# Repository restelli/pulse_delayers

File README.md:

# Pulse delay.
This is a PCB to test four delay chips.
I put it together in a couple of hours for a dirty test, but if further refined it could become a handy lab tool.
(Note that the SMA and power connectors are intentionally placed on the wrong side of the board)

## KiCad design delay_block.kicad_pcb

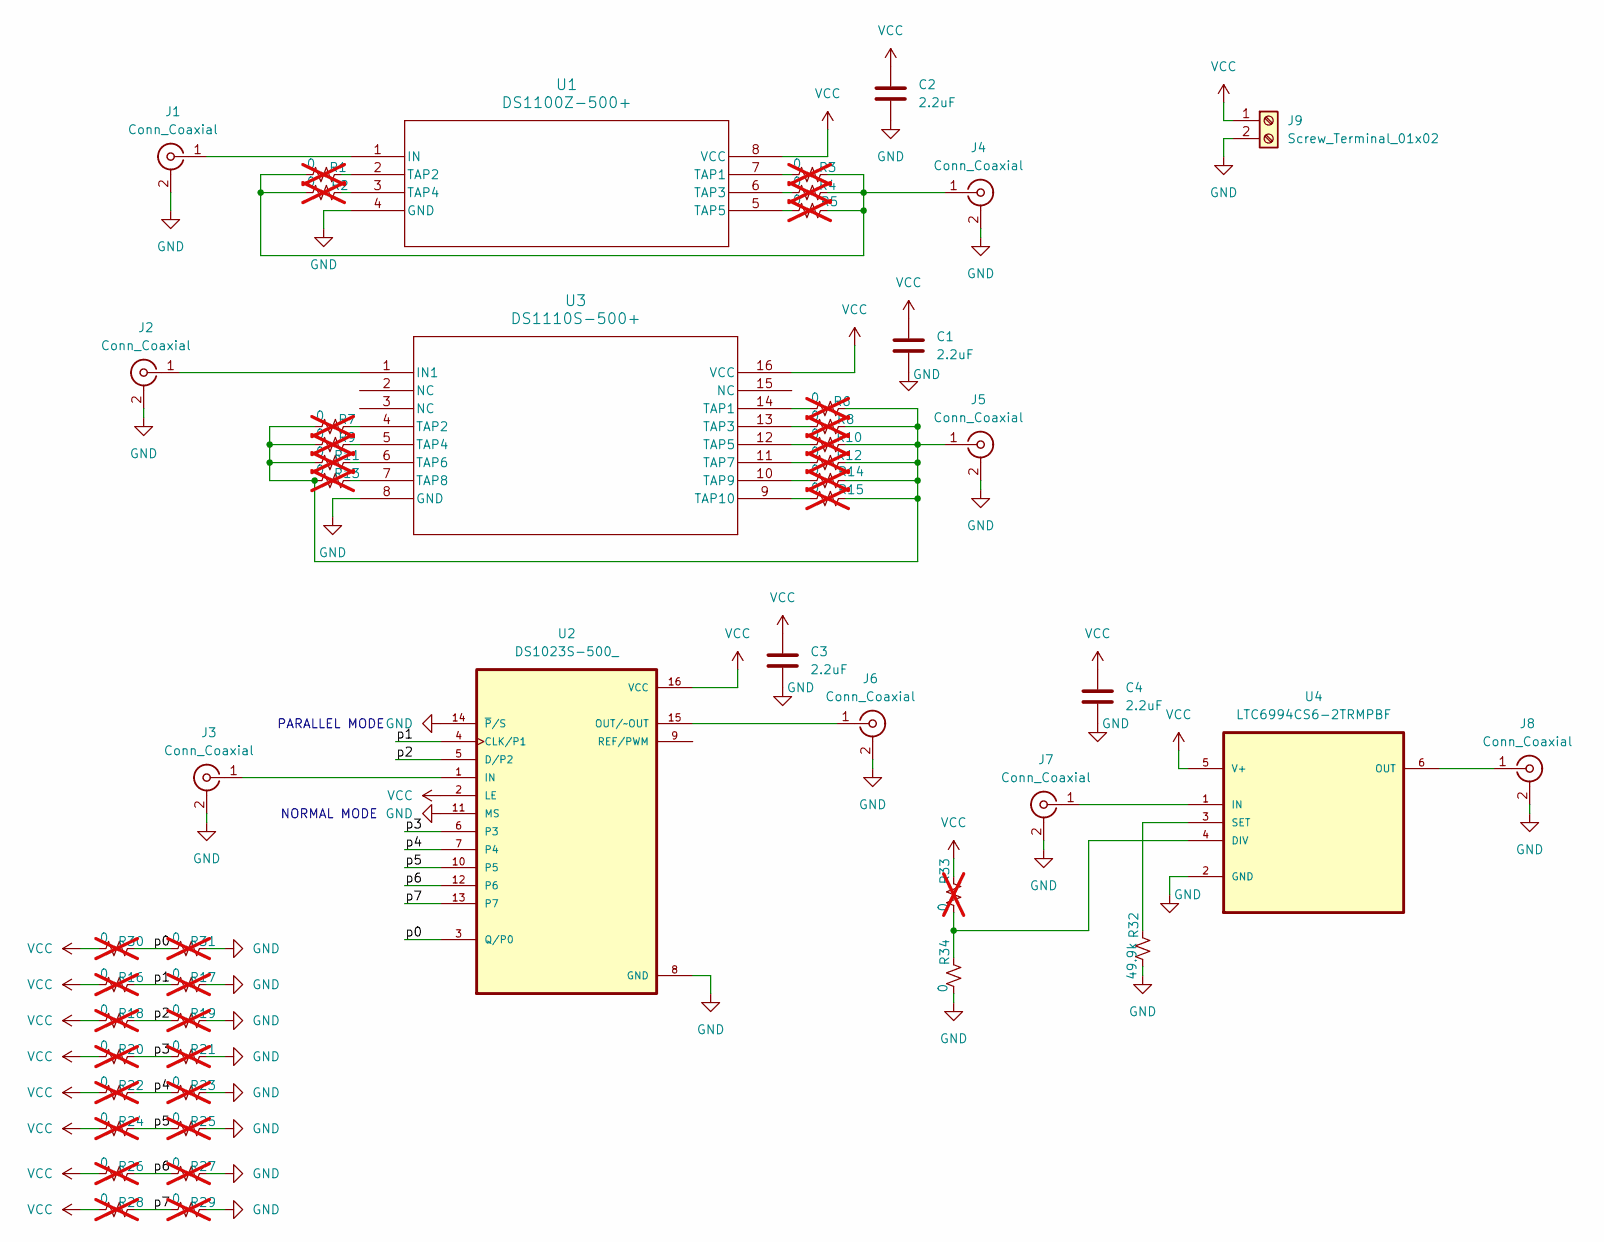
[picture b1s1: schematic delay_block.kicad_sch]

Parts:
C1, C2, C3, C4: 2.2uF; C_0805_2012Metric
J1, J2, J3, J4, J5, J6, J7, J8: Conn_Coaxial; SMA_Amphenol_901-144_Vertical
J9: Screw_Terminal_01x02; TerminalBlock_4Ucon_1x02_P3.50mm_Horizontal
R1, R2, R3, R4, R5, R6, R7, R8, R9, R10, R11, R12, R13, R14, R15, R16, R17, R18, R19, R20, R21, R22, R23, R24, R25, R26, R27, R28, R29, R30, R31, R33: 0; R_0603_1608Metric; not fitted
R32: 49.9k; R_0603_1608Metric
R34: 0; R_0603_1608Metric
U1: DS1100Z-500+; 21-0041B_8_MXM
U2: DS1023S-500_; SOIC127P1032X265-16N
U3: DS1110S-500+; 21-0042B_16_MXM
U4: LTC6994CS6-2TRMPBF; SOT95P280X100-6N; MPN LTC6994CS6-2#TRMPBF

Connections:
/p0: R30.2, R31.1, U2.3 (Q/P0)
/p1: R16.2, R17.1, U2.4 (CLK/P1)
/p2: R18.2, R19.1, U2.5 (D/P2)
/p3: R20.2, R21.1, U2.6 (P3)
/p4: R22.2, R23.1, U2.7 (P4)
/p5: R24.2, R25.1, U2.10 (P5)
/p6: R26.2, R27.1, U2.12 (P6)
/p7: R28.2, R29.1, U2.13 (P7)
GND: C1.2, C2.2, C3.2, C4.2, J1.2 (Ext), J2.2 (Ext), J3.2 (Ext), J4.2 (Ext), J5.2 (Ext), J6.2 (Ext), J7.2 (Ext), J8.2 (Ext), J9.2, R17.2, R19.2, R21.2, R23.2, R25.2, R27.2, R29.2, R31.2, R32.1, R34.1, U1.4 (GND), U2.8 (GND), U2.11 (MS), U2.14 (~P/S), U3.8 (GND), U4.2 (GND)
unnamed: J1.1 (In), U1.1 (IN)
unnamed: J2.1 (In), U3.1 (IN1)
unnamed: J3.1 (In), U2.1 (IN)
unnamed: J4.1 (In), R1.1, R2.1, R3.2, R4.2, R5.2
unnamed: J5.1 (In), R6.2, R7.1, R8.2, R9.1, R10.2, R11.1, R12.2, R13.1, R14.2, R15.2
unnamed: J6.1 (In), U2.15 (OUT/~OUT)
unnamed: J7.1 (In), U4.1 (IN)
unnamed: J8.1 (In), U4.6 (OUT)
unnamed: R3.1, U1.7 (TAP1)
unnamed: R1.2, U1.2 (TAP2)
unnamed: R4.1, U1.6 (TAP3)
unnamed: R2.2, U1.3 (TAP4)
unnamed: R5.1, U1.5 (TAP5)
unnamed: R6.1, U3.14 (TAP1)
unnamed: R7.2, U3.4 (TAP2)
unnamed: R8.1, U3.13 (TAP3)
unnamed: R9.2, U3.5 (TAP4)
unnamed: R10.1, U3.12 (TAP5)
unnamed: R11.2, U3.6 (TAP6)
unnamed: R12.1, U3.11 (TAP7)
unnamed: R13.2, U3.7 (TAP8)
unnamed: R14.1, U3.10 (TAP9)
unnamed: R15.1, U3.9 (TAP10)
unnamed: R33.1, R34.2, U4.4 (DIV)
unnamed: R32.2, U4.3 (SET)
VCC: C1.1, C2.1, C3.1, C4.1, J9.1, R16.1, R18.1, R20.1, R22.1, R24.1, R26.1, R28.1, R30.1, R33.2, U1.8 (VCC), U2.2 (LE), U2.16 (VCC), U3.16 (VCC), U4.5 (V+)

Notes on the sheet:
NORMAL MODE
PARALLEL MODE

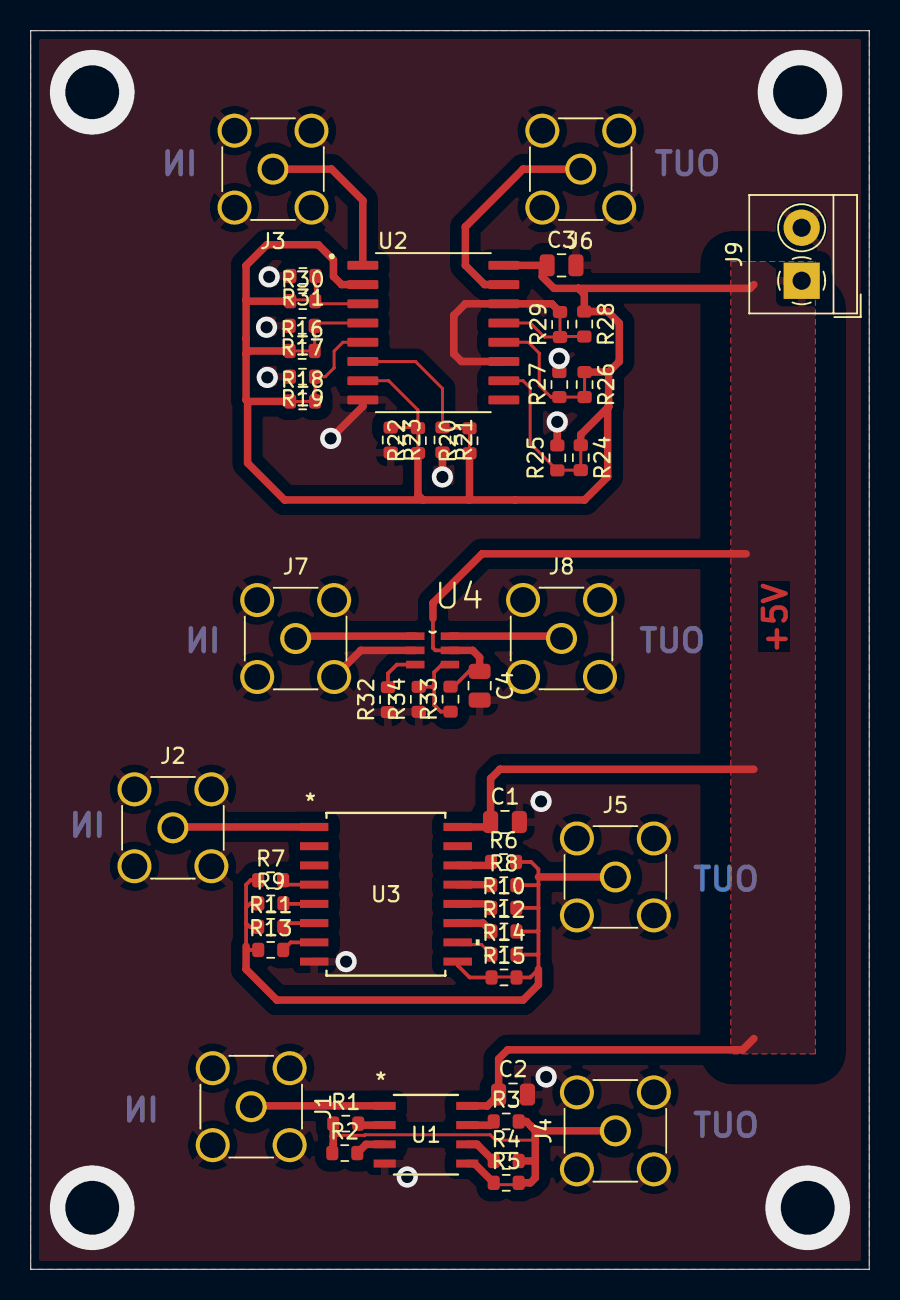
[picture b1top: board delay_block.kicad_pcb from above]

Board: 2 copper layers, 55.4 x 81.8 mm, 51 parts (0 on the bottom side), 35 nets.

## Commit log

2024-07-10 initial files
2024-07-10 hardwired jumpers to set ~500us everywhere
2024-07-10 Set LTC6994 for 1us delay: R32=50k R33 open R34 shorted
2024-07-10 small esthetic adjustment in schematic
2024-07-10 Added attributes DNP
